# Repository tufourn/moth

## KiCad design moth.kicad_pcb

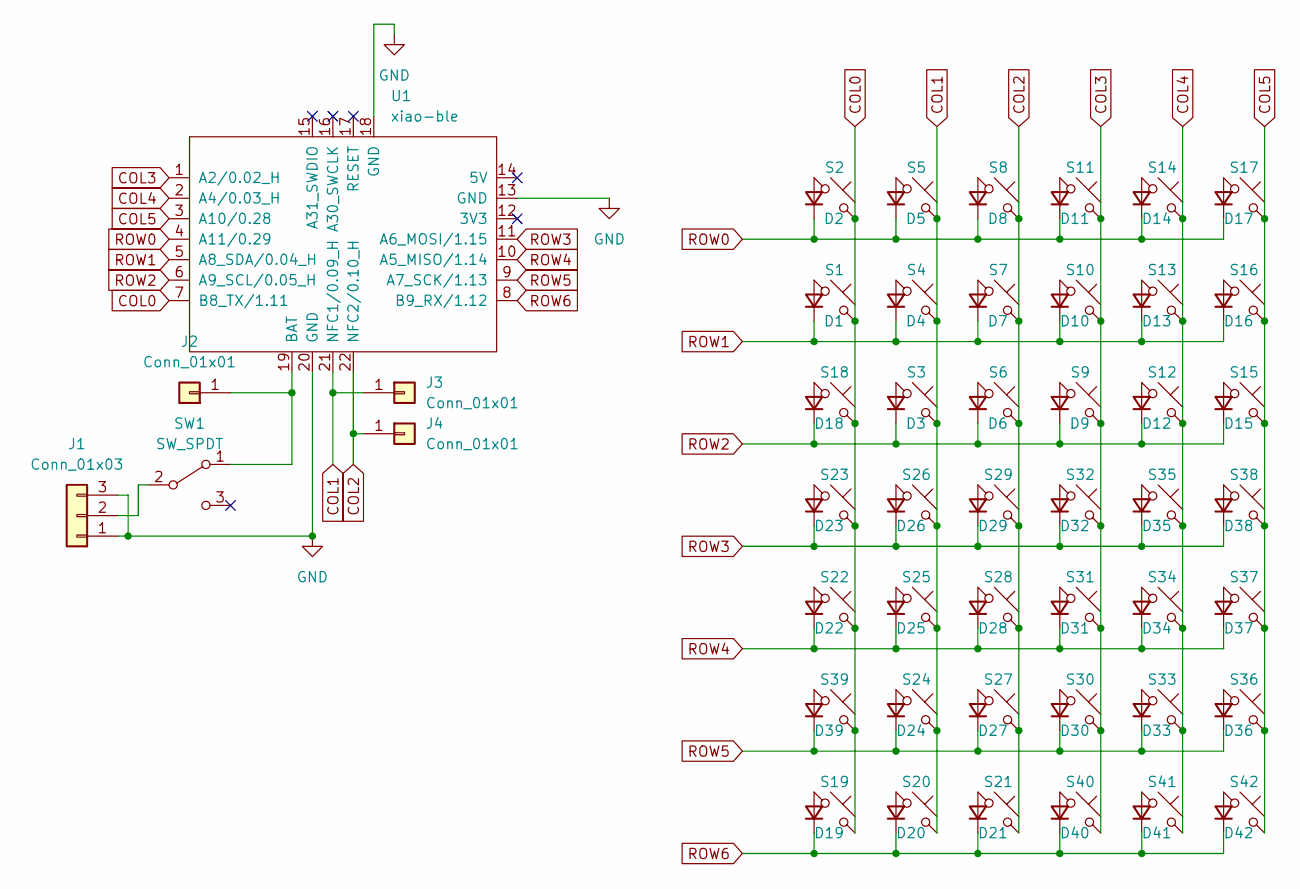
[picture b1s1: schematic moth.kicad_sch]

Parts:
D1, D2, D3, D4, D5, D6, D7, D8, D9, D10, D11, D12, D13, D14, D15, D16, D17, D18, D19, D20, D21, D22, D23, D24, D25, D26, D27, D28, D29, D30, D31, D32, D33, D34, D35, D36, D37, D38, D39, D40, D41, D42: 1N4148; D_SOD-123-back
J1: Conn_01x03; JST_PH_S3B-PH-K_1x03_P2.00mm_Horizontal
J2, J3, J4: Conn_01x01; SolderWirePad_1x01_SMD_1x2mm
S1, S2, S3, S4, S5, S6, S7, S8, S9, S10, S11, S12, S13, S14, S15, S16, S17, S18, S19, S20, S21, S22, S23, S24, S25, S26, S27, S28, S29, S30, S31, S32, S33, S34, S35, S36, S37, S38, S39, S40, S41, S42: Choc; pg1350-B
SW1: SW_SPDT; SW_SPDT_PCM12
U1: xiao-ble; xiao-ble-smd-cutout

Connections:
COL0: S1.2, S2.2, S18.2, S19.2, S22.2, S23.2, S39.2, U1.7 (B8_TX/1.11)
COL1: J3.1, S3.2, S4.2, S5.2, S20.2, S24.2, S25.2, S26.2, U1.21 (NFC1/0.09_H); also elsewhere on the board
COL2: J4.1, S6.2, S7.2, S8.2, S21.2, S27.2, S28.2, S29.2, U1.22 (NFC2/0.10_H)
COL3: S9.2, S10.2, S11.2, S30.2, S31.2, S32.2, S40.2, U1.1 (A2/0.02_H)
COL4: S12.2, S13.2, S14.2, S33.2, S34.2, S35.2, S41.2, U1.2 (A4/0.03_H)
COL5: S15.2, S16.2, S17.2, S36.2, S37.2, S38.2, S42.2, U1.3 (A10/0.28)
GND: J1.1, J1.3, U1.13 (GND), U1.18 (GND), U1.20 (GND)
unnamed: D1.2 (A), S1.1
unnamed: D2.2 (A), S2.1
unnamed: D3.2 (A), S3.1
unnamed: D4.2 (A), S4.1
unnamed: D5.2 (A), S5.1
unnamed: D6.2 (A), S6.1
unnamed: D7.2 (A), S7.1
unnamed: D8.2 (A), S8.1
unnamed: D9.2 (A), S9.1
unnamed: D10.2 (A), S10.1
unnamed: D11.2 (A), S11.1
unnamed: D12.2 (A), S12.1
unnamed: D13.2 (A), S13.1
unnamed: D14.2 (A), S14.1
unnamed: D15.2 (A), S15.1
unnamed: D16.2 (A), S16.1
unnamed: D17.2 (A), S17.1
unnamed: D18.2 (A), S18.1
unnamed: D19.2 (A), S19.1
unnamed: D20.2 (A), S20.1
unnamed: D21.2 (A), S21.1
unnamed: D22.2 (A), S22.1
unnamed: D23.2 (A), S23.1
unnamed: D24.2 (A), S24.1
unnamed: D25.2 (A), S25.1
unnamed: D26.2 (A), S26.1
unnamed: D27.2 (A), S27.1
unnamed: D28.2 (A), S28.1
unnamed: D29.2 (A), S29.1
unnamed: D30.2 (A), S30.1
unnamed: D31.2 (A), S31.1
unnamed: D32.2 (A), S32.1
unnamed: D33.2 (A), S33.1
unnamed: D34.2 (A), S34.1
unnamed: D35.2 (A), S35.1
unnamed: D36.2 (A), S36.1
unnamed: D37.2 (A), S37.1
unnamed: D38.2 (A), S38.1
unnamed: D39.2 (A), S39.1
unnamed: D40.2 (A), S40.1
unnamed: D41.2 (A), S41.1
unnamed: D42.2 (A), S42.1
unnamed: J1.2, SW1.2 (B)
unnamed 50: J2.1, SW1.1 (A), U1.19 (BAT); also elsewhere on the board
ROW0: D2.1 (K), D5.1 (K), D8.1 (K), D11.1 (K), D14.1 (K), D17.1 (K), U1.4 (A11/0.29)
ROW1: D1.1 (K), D4.1 (K), D7.1 (K), D10.1 (K), D13.1 (K), D16.1 (K), U1.5 (A8_SDA/0.04_H)
ROW2: D3.1 (K), D6.1 (K), D9.1 (K), D12.1 (K), D15.1 (K), D18.1 (K), U1.6 (A9_SCL/0.05_H)
ROW3: D23.1 (K), D26.1 (K), D29.1 (K), D32.1 (K), D35.1 (K), D38.1 (K), U1.11 (A6_MOSI/1.15)
ROW4: D22.1 (K), D25.1 (K), D28.1 (K), D31.1 (K), D34.1 (K), D37.1 (K), U1.10 (A5_MISO/1.14)
ROW5: D24.1 (K), D27.1 (K), D30.1 (K), D33.1 (K), D36.1 (K), D39.1 (K), U1.9 (A7_SCK/1.13)
ROW6: D19.1 (K), D20.1 (K), D21.1 (K), D40.1 (K), D41.1 (K), D42.1 (K), U1.8 (B9_RX/1.12)

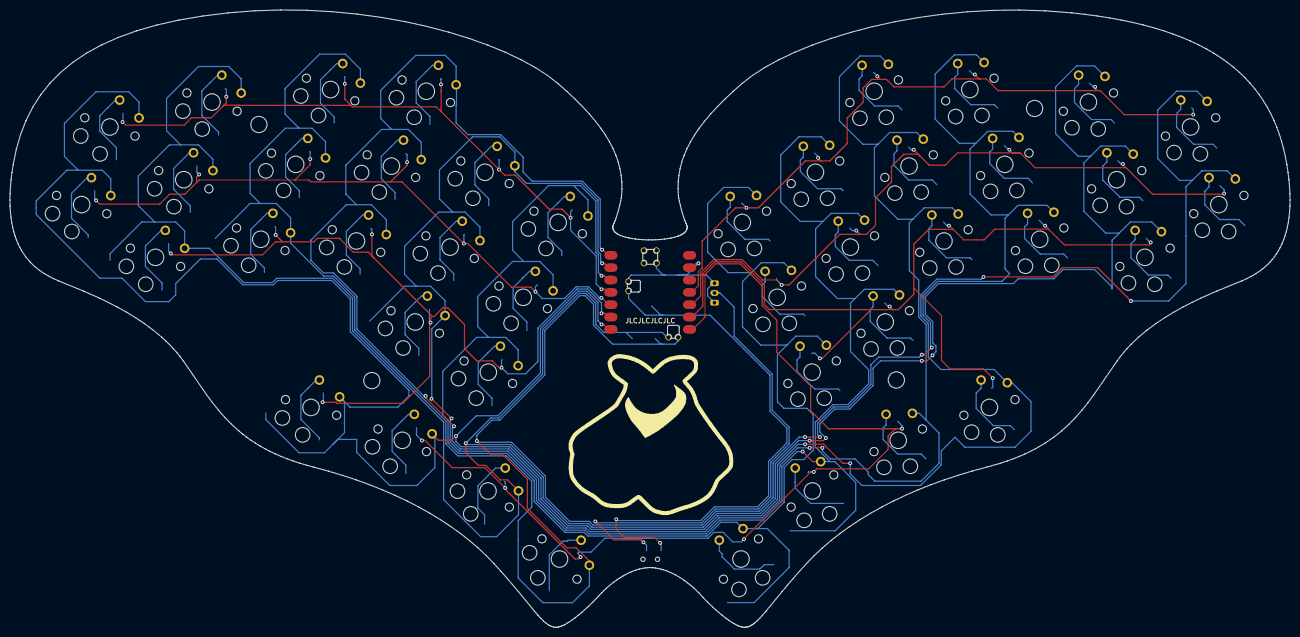
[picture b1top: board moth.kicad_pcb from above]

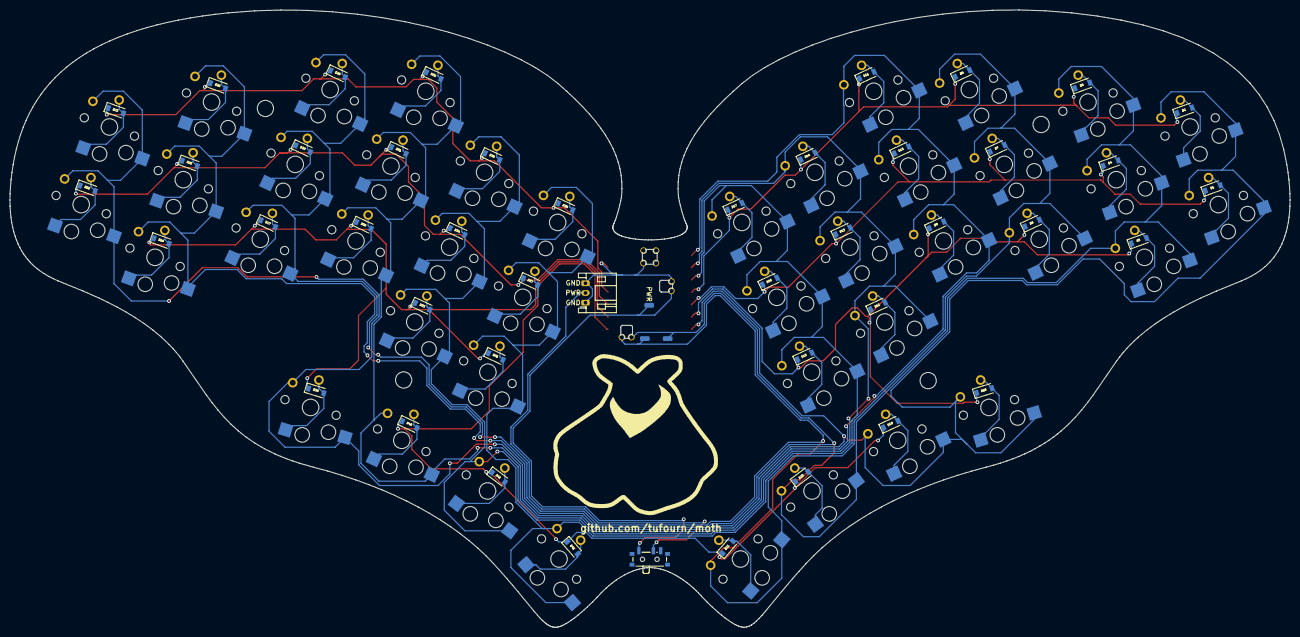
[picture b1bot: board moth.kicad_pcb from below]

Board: 2 copper layers, 263.4 x 127.0 mm, 90 parts (5 on the bottom side), 58 nets.

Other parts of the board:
COL1: Conn_01x01; SolderWirePad_1x01_SMD_1x2mm
PWR: Conn_01x01; SolderWirePad_1x01_SMD_1x2mm

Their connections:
COL1: COL1.1; also elsewhere on the board
unnamed 50: PWR.1; also elsewhere on the board

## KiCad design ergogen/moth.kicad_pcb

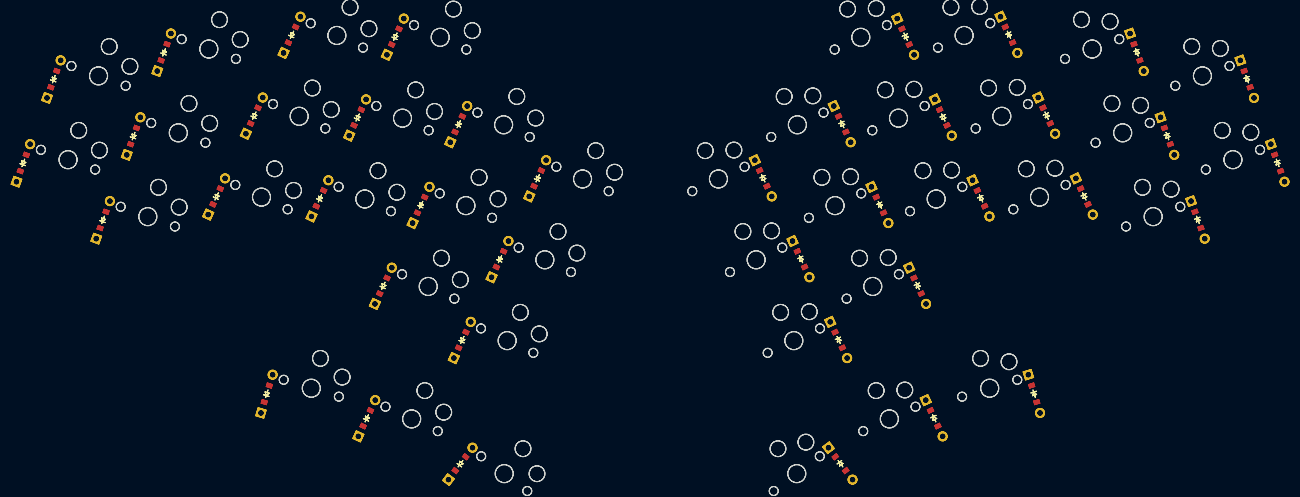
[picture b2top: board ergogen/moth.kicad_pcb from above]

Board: 2 copper layers, 160 parts (0 on the bottom side), 40 nets, no tracks yet.

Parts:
D1, D2, D3, D4, D5, D6, D7, D8, D9, D10, D11, D12, D13, D14, D15, D16, D17, D18, D19, D20, D21, D22, D23, D24, D25, D26, D27, D28, D29, D30, D31, D32, D33, D34, D35, D36, D37, D38, D39, D40, D41, D42, D43, D44, D45, D46, D47, D48, D49, D50, D51, D52, D53, D54, D55, D56, D57, D58, D59, D60, D61, D62, D63, D64, D65, D66, D67, D68, D69, D70, D71, D72, D73, D74, D75, D76, D77, D78, D79, D80: ComboDiode
S1, S2, S3, S4, S5, S6, S7, S8, S9, S10, S11, S12, S13, S14, S15, S16, S17, S18, S19, S20, S21, S22, S23, S24, S25, S26, S27, S28, S29, S30, S31, S32, S33, S34, S35, S36, S37, S38, S39, S40, S41, S42, S43, S44, S45, S46, S47, S48, S49, S50, S51, S52, S53, S54, S55, S56, S57, S58, S59, S60, S61, S62, S63, S64, S65, S66, S67, S68, S69, S70, S71, S72, S73, S74, S75, S76, S77, S78, S79, S80: PG1350

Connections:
far_hi: D20.2, D80.2, S20.1, S80.1
home_hi: D19.2, D79.2, S19.1, S79.1
index_bot: D14.2, D74.2, S14.1, S74.1
index_mid: D13.2, D73.2, S13.1, S73.1
index_top: D12.2, D72.2, S12.1, S72.1
inner_bot: D17.2, D77.2, S17.1, S77.1
inner_mid: D16.2, D76.2, S16.1, S76.1
inner_top: D15.2, D75.2, S15.1, S75.1
mid_bot: D11.2, D71.2, S11.1, S71.1
mid_mid: D10.2, D70.2, S10.1, S70.1
mid_top: D9.2, D69.2, S9.1, S69.1
mirror_far_hi: D40.2, D60.2, S40.1, S60.1
mirror_home_hi: D39.2, D59.2, S39.1, S59.1
mirror_index_bot: D34.2, D54.2, S34.1, S54.1
mirror_index_mid: D33.2, D53.2, S33.1, S53.1
mirror_index_top: D32.2, D52.2, S32.1, S52.1
mirror_inner_bot: D37.2, D57.2, S37.1, S57.1
mirror_inner_mid: D36.2, D56.2, S36.1, S56.1
mirror_inner_top: D35.2, D55.2, S35.1, S55.1
mirror_mid_bot: D31.2, D51.2, S31.1, S51.1
mirror_mid_mid: D30.2, D50.2, S30.1, S50.1
mirror_mid_top: D29.2, D49.2, S29.1, S49.1
mirror_near_hi: D38.2, D58.2, S38.1, S58.1
mirror_outer_bot: D22.2, D42.2, S22.1, S42.1
mirror_outer_mid: D21.2, D41.2, S21.1, S41.1
mirror_pinky_bot: D25.2, D45.2, S25.1, S45.1
mirror_pinky_mid: D24.2, D44.2, S24.1, S44.1
mirror_pinky_top: D23.2, D43.2, S23.1, S43.1
mirror_ring_bot: D28.2, D48.2, S28.1, S48.1
mirror_ring_mid: D27.2, D47.2, S27.1, S47.1
mirror_ring_top: D26.2, D46.2, S26.1, S46.1
near_hi: D18.2, D78.2, S18.1, S78.1
outer_bot: D2.2, D62.2, S2.1, S62.1
outer_mid: D1.2, D61.2, S1.1, S61.1
pinky_bot: D5.2, D65.2, S5.1, S65.1
pinky_mid: D4.2, D64.2, S4.1, S64.1
pinky_top: D3.2, D63.2, S3.1, S63.1
ring_bot: D8.2, D68.2, S8.1, S68.1
ring_mid: D7.2, D67.2, S7.1, S67.1
ring_top: D6.2, D66.2, S6.1, S66.1

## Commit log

2023-03-07 initial
2023-03-09 completed routing
2023-03-09 update ergogen configs
2023-03-09 added moth artwork
2023-03-10 add fill
2023-03-10 update gerbers
